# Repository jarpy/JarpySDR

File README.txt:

JarpySDR - A Tayloe Detector board for Software Defined Radio.

This is a simple SDR frontend using all through-hole components.

It requires an off-board square-wave oscillator/clock running at F*4, where F is the radio frequency to be recieved. The design is pin compatible with WA6UFQ's Si570 oscillator card, and provides an I2C pass-through header with which to program the Si570.

You don't have to use the Si570 board however. You can clock it with any square-wave source you have handy.

The design is derived from the G0NQE Acorn SDR receiver.

Links:
  Si570 oscillator board
  http://home.roadrunner.com/~wa6ufq/universal_vfo_controller.html

  G0NQE Acorn SDR
  http://www.g0nqe.co.uk/projects/g0nqe-acorn_sdr_receiver

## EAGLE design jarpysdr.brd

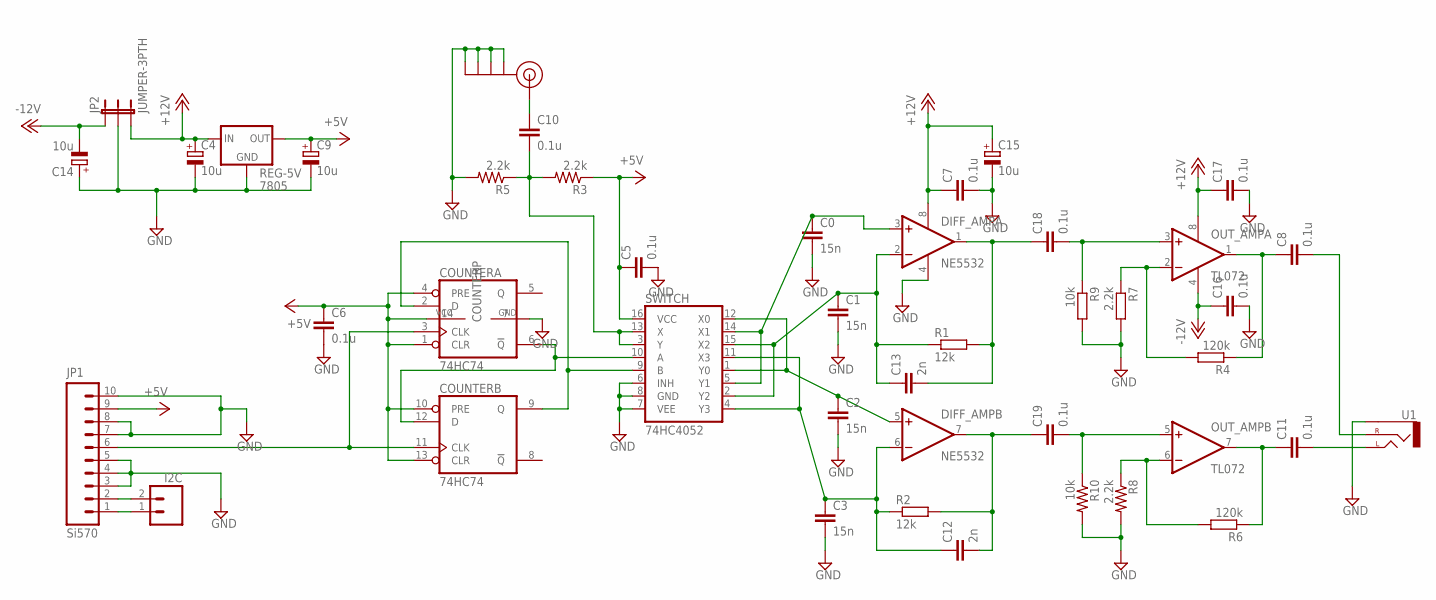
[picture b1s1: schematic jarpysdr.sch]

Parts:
ANTENNA: SMA_EDGE; SMA-EDGE
C0, C1, C2, C3: 15n; C025-024X044
C4, C9, C14, C15: 10u; E2,5-6
C5, C6, C7, C16, C17: 0.1u; C025-025X050
C8, C11, C18, C19: 0.1u; C050-025X075
C10: 0.1u; C025-024X044
C12, C13: 2n; C025-024X044
COUNTER: 74HC74; DIL14
DIFF_AMP: NE5532; DIL08
I2C: M02PTH; 1X02
JP1: Si570; 1X10
JP2: JUMPER-3PTH; 1X03
OUT_AMP: TL072; DIL08
R1, R2: 12k; 0204/7
R3, R5, R7, R8: 2.2k; 0204/7
R4, R6: 120k; 0204/7
R9, R10: 10k; 0204/7
REG-5V: 7805; 78XXS
SWITCH: 74HC4052; DIL16
U1: AUDIO-JACKPTH; AUDIO-JACK

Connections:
+5V: C5.1, C6.1, C9.+, COUNTER.1 (CLR), COUNTER.4 (PRE), COUNTER.10 (PRE), COUNTER.13 (CLR), COUNTER.14 (VCC), JP1.9, R3.1, REG-5V.OUT, SWITCH.16 (VCC)
+12V: C4.+, C7.1, C15.+, C17.1, DIFF_AMP.8 (V+), JP2.3, OUT_AMP.8 (V+), REG-5V.IN
-12V: C14.-, C16.1, JP2.1, OUT_AMP.4 (V-)
C-180DEG: C1.1, C13.1, DIFF_AMP.2 (-IN), R1.1, SWITCH.2 (Y2), SWITCH.15 (X2)
CLK: COUNTER.3 (CLK), COUNTER.11 (CLK), JP1.6
GND: ANTENNA.GND@0 (GND), ANTENNA.GND@1 (GND), ANTENNA.GND@2 (GND), ANTENNA.GND@3 (GND), C0.2, C1.2, C2.2, C3.2, C4.-, C5.2, C6.2, C7.2, C9.-, C14.+, C15.-, C16.2, C17.2, COUNTER.7 (GND), DIFF_AMP.4 (V-), JP1.3, JP1.4, JP1.5, JP1.7, JP1.8, JP1.10, JP2.2, R5.2, R7.2, R8.2, R9.2, R10.2, REG-5V.GND, SWITCH.6 (INH), SWITCH.7 (VEE), SWITCH.8 (GND), U1.SLEEVE
unnamed: C2.1, DIFF_AMP.5 (+IN), SWITCH.1 (Y0), SWITCH.12 (X0)
unnamed: COUNTER.2 (D), COUNTER.9 (Q), SWITCH.9 (B)
unnamed: COUNTER.6 (!Q), COUNTER.12 (D), SWITCH.10 (A)
unnamed: C10.2, R3.2, R5.1, SWITCH.3 (Y), SWITCH.13 (X)
unnamed: C0.1, DIFF_AMP.3 (+IN), SWITCH.5 (Y1), SWITCH.14 (X1)
unnamed: C13.2, C18.1, DIFF_AMP.1 (OUT), R1.2
unnamed: ANTENNA.SIG (SIGNAL), C10.1
unnamed: C11.2, U1.TIP (LEFT)
unnamed: C8.2, U1.RING (RIGHT)
unnamed: C12.2, C19.1, DIFF_AMP.7 (OUT), R2.2
unnamed: C8.1, OUT_AMP.1 (OUT), R4.1
unnamed: OUT_AMP.2 (-IN), R4.2, R7.1
unnamed: C11.1, OUT_AMP.7 (OUT), R6.1
unnamed: C3.1, C12.1, DIFF_AMP.6 (-IN), R2.1, SWITCH.4 (Y3), SWITCH.11 (X3)
unnamed: OUT_AMP.6 (-IN), R6.2, R8.1
unnamed: I2C.1, JP1.1
unnamed: I2C.2, JP1.2
unnamed: C18.2, OUT_AMP.3 (+IN), R9.1
unnamed: C19.2, OUT_AMP.5 (+IN), R10.1

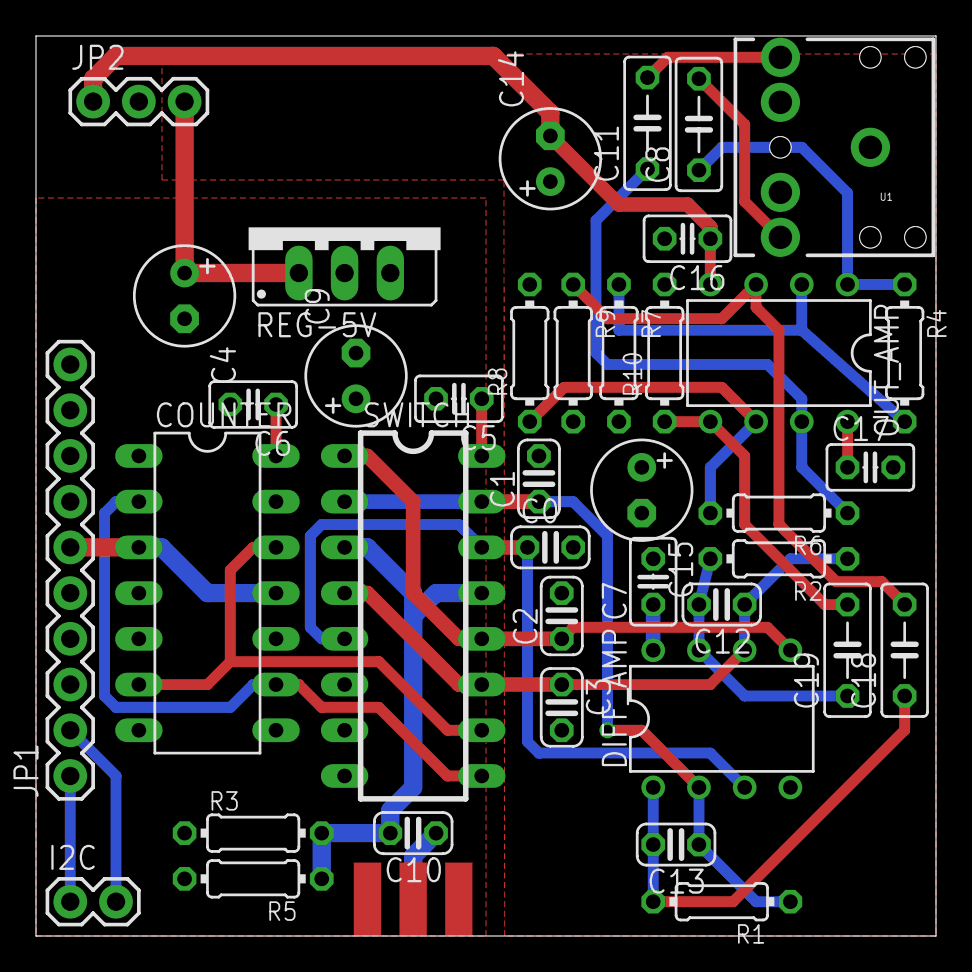
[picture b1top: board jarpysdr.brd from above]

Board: 2 copper layers, 50.0 x 50.0 mm, 40 parts (0 on the bottom side), 25 nets.

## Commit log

2011-10-29 First prototype.
2012-03-24 - Replace with audio and antenna connectors with jacks available from SparkFun.
    - Make room for a heatsink on the 7805 regulator.
    - Move oscillator daughter-board connecter to edge. (Use right-angle
    female header).
2012-03-24 Re-align all parts to a 0.1inch grid.
2012-03-24 Double-sided layout.
2012-03-24 Move osc connector to left edge.
2012-03-24 Gave some love to the ground plane.
2012-03-24 Added power planes.
2012-03-24 Moved drawing to origin.
2012-03-24 Final physical layout for fab.
2012-03-24 Set up silkscreen.
2012-03-24 Release to fab.
2012-03-24 Really-truly final version for release. Sent to fab. Yay.
2012-04-02 Add a README.
2012-04-06 AC couple the two opamp stages.
2012-04-11 Fixed some typoes and added link to the G0NQE-Acorn.
2012-04-25 - Increased final stage gain. - Increased bandwidth (smaller sampling capacitors).
2012-04-25 Align output jack to board edge.
2012-04-25 Physical layout for inter-stage AC coupling.
2012-04-25 Put NE5532 differential amplifier on a single supply.
2012-04-29 New layout. 50x50mm board.
